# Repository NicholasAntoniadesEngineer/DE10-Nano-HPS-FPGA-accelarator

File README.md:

# DE10-Nano HPS-FPGA Accelerator

FPGA-accelerated IEEE 754 floating-point calculator on the Intel Cyclone V SoC (DE10-Nano). The FPGA fabric implements ADD, SUB, MUL, and DIV in pure RTL with a 7-cycle pipeline. The HPS (dual-core ARM Cortex-A9) runs Debian Linux and communicates with the calculator IP over the Lightweight HPS-to-FPGA Avalon-MM bridge.

## Prerequisites

- **Docker Desktop** (with Rosetta 2 on Apple Silicon)
- **Git** (with LFS: `git lfs install`)
- **50 GB+ free disk space** (Quartus 18.1 image + build artifacts)
- **DE10-Nano** + MicroSD card (8 GB+)

## Build

All builds run inside a Docker container (Quartus 18.1 + ARM GCC). No native toolchain needed.

```bash
cd docker

# First time: build the Docker image (~20 min)
./scripts/setup.sh

# Full system build: FPGA + kernel + rootfs + SD image (~60 min first time)
./scripts/docker-build.sh

# Or build individual components
./scripts/docker-build.sh fpga          # FPGA bitstream only (~23 min)
./scripts/docker-build.sh applications  # HPS applications only (~1 min)
```

**Output**: `HPS/linux_image/build/de10-nano-custom.img`

## Flash SD Card (macOS)

```bash
diskutil list                                            # identify SD card (e.g. /dev/disk4)
diskutil unmountDisk force /dev/diskN                     # unmount all partitions
sudo dd if=HPS/linux_image/build/de10-nano-custom.img of=/dev/rdiskN bs=4m
```

> Terminal must have **Full Disk Access** (System Settings > Privacy & Security > Full Disk Access).
> The disk number changes on replug -- always run `diskutil list` first.

## Prepare DE10-Nano

1. **Set MSEL DIP switch (SW10)** for HPS FPGA programming mode. Wrong MSEL = FPGA loads but registers return 0x0.
2. Insert SD card, connect USB cable (Ethernet + UART), power on.
3. Boot takes ~10 seconds. LEDs animate during `boot-led` startup.

> After changing DIP switches, **power cycle** the board (reboot is not enough -- MSEL is sampled at power-on).

## Connect via SSH

```bash
# Auto-detect USB Ethernet, configure interface, and SSH in
./scripts/ssh-to-board.sh

# Or manually (interface name varies -- check ifconfig)
sudo ifconfig en13 192.168.2.1 netmask 255.255.255.0
ssh root@192.168.2.2   # password: root
```

### Share Internet with Board

```bash
# Set up NAT so the board can reach the internet through your Mac
./scripts/share-internet.sh

# Tear down when done
./scripts/share-internet.sh --stop
```

## Run Applications

### Calculator Test Suite
```bash
calculator_test        # run all tests with 500 ms LED delays
calculator_test -q     # quick mode (no delays)
calculator_test -v     # verbose (register-level output)
```

### Calculator Demo (auto-starts at boot)
```bash
systemctl status calculator-demo     # check status
journalctl -u calculator-demo -f     # watch live output
```

### Boot LED (runs once at boot)
```bash
systemctl status boot-led            # check status
journalctl -u boot-led               # view log
```

### Register Access
```bash
devmem2 0xff20003c w    # read VERSION register (expect 0x00010001)
```

### Verify FPGA Bridges
```bash
cat /sys/class/fpga_bridge/*/state   # expect: "enabled"
```

## Project Structure

```
Makefile                  # Top-level orchestration
FPGA/
  quartus/                # Quartus project files + QSys system
  hdl/                    # Top-level Verilog (DE10_NANO_SoC_GHRD.v)
  ip/custom/calculator/   # Calculator IP (8 Verilog files + _hw.tcl)
  ip/custom/template/     # Template IP scaffold for new accelerators
  mk/                     # Modular Makefile fragments (qsys, quartus, etc.)
  generated/              # QSys-generated HDL (overlaid by qsys_check.sh)
  build/output_files/     # Quartus output (.rbf for SD card)
HPS/
  drivers/calculator/     # UIO-based calculator driver (/dev/uioN + mmap)
  drivers/fpga_uio/       # Shared UIO library (generic mmap abstraction)
  drivers/template/       # UIO driver template for new IP
  libs/logger/            # Shared logging library
  applications/
    calculator_test/      # Test suite (33 test cases)
    calculator_demo/      # Demo service (systemd, auto-start)
    boot_led/             # LED heartbeat at boot (systemd)
  tools/devmem2/          # /dev/mem read/write tool (cross-compiled)
  linux_image/
    kernel/               # Linux kernel (socfpga_defconfig)
    kernel/dts/           # Device tree sources (single source of truth)
    rootfs/               # Debian rootfs (debootstrap + overlays)
    bootloader/           # U-Boot + SPL + device tree
    scripts/              # SD image creation, rootfs build
scripts/
  generate-ip-framework.sh  # Scaffold new FPGA IP + QSys + UIO driver
  generate-app-framework.sh # Scaffold new HPS application + systemd service
  new_ip.sh                 # Symlink to generate-ip-framework.sh
  ssh-to-board.sh           # Auto-detect USB Ethernet, configure, SSH in
  share-internet.sh         # NAT setup: share Mac internet with board
  env-check.sh              # Validate host build environment
docker/
  scripts/                # setup.sh, docker-build.sh, docker-clean.sh
  Dockerfile              # Quartus 18.1 + ARM GCC container
documentation/
  deployment_guide.md     # Detailed deployment walkthrough
  hps_fpga_communication.md
```

## Troubleshooting

| Symptom | Cause | Fix |
|---------|-------|-----|
| `devmem2 0xff20003c w` returns `0x00000000` | MSEL DIP switch wrong | Set SW10 correctly, **power cycle** |
| All bridges show "disabled" | U-Boot didn't enable bridges | Check boot.scr, verify FPGA loaded |
| `calculator_test` all fail same result | Calculator not responding | Check bridge state, re-flash FPGA |
| SSH connection refused | USB Ethernet not configured | Run `ifconfig en13 192.168.2.1 ...` |
| `dd: permission denied` | Missing Full Disk Access | Add Terminal to Full Disk Access |
| Board can't reach internet | NAT not configured | Run `./scripts/share-internet.sh` |

## References

- [Deployment Guide](documentation/deployment_guide.md) -- step-by-step build and flash
- [Docker Build Environment](docker/README.md) -- container setup and scripts
- [FPGA-HPS Communication](documentation/hps_fpga_communication.md) -- register map and bridge details
- [DE10-Nano User Manual](documentation/references/DE10-Nano_User_manual_a_b.pdf)
- [Terasic DE10-Nano](https://www.terasic.com.tw/cgi-bin/page/archive.pl?Language=English&CategoryNo=165&No=1046#contents)
- [Cyclone V HPS Register Map](https://www.intel.com/content/www/us/en/programmable/hps/cyclone-v/hps.html#sfo1418687413697.html)

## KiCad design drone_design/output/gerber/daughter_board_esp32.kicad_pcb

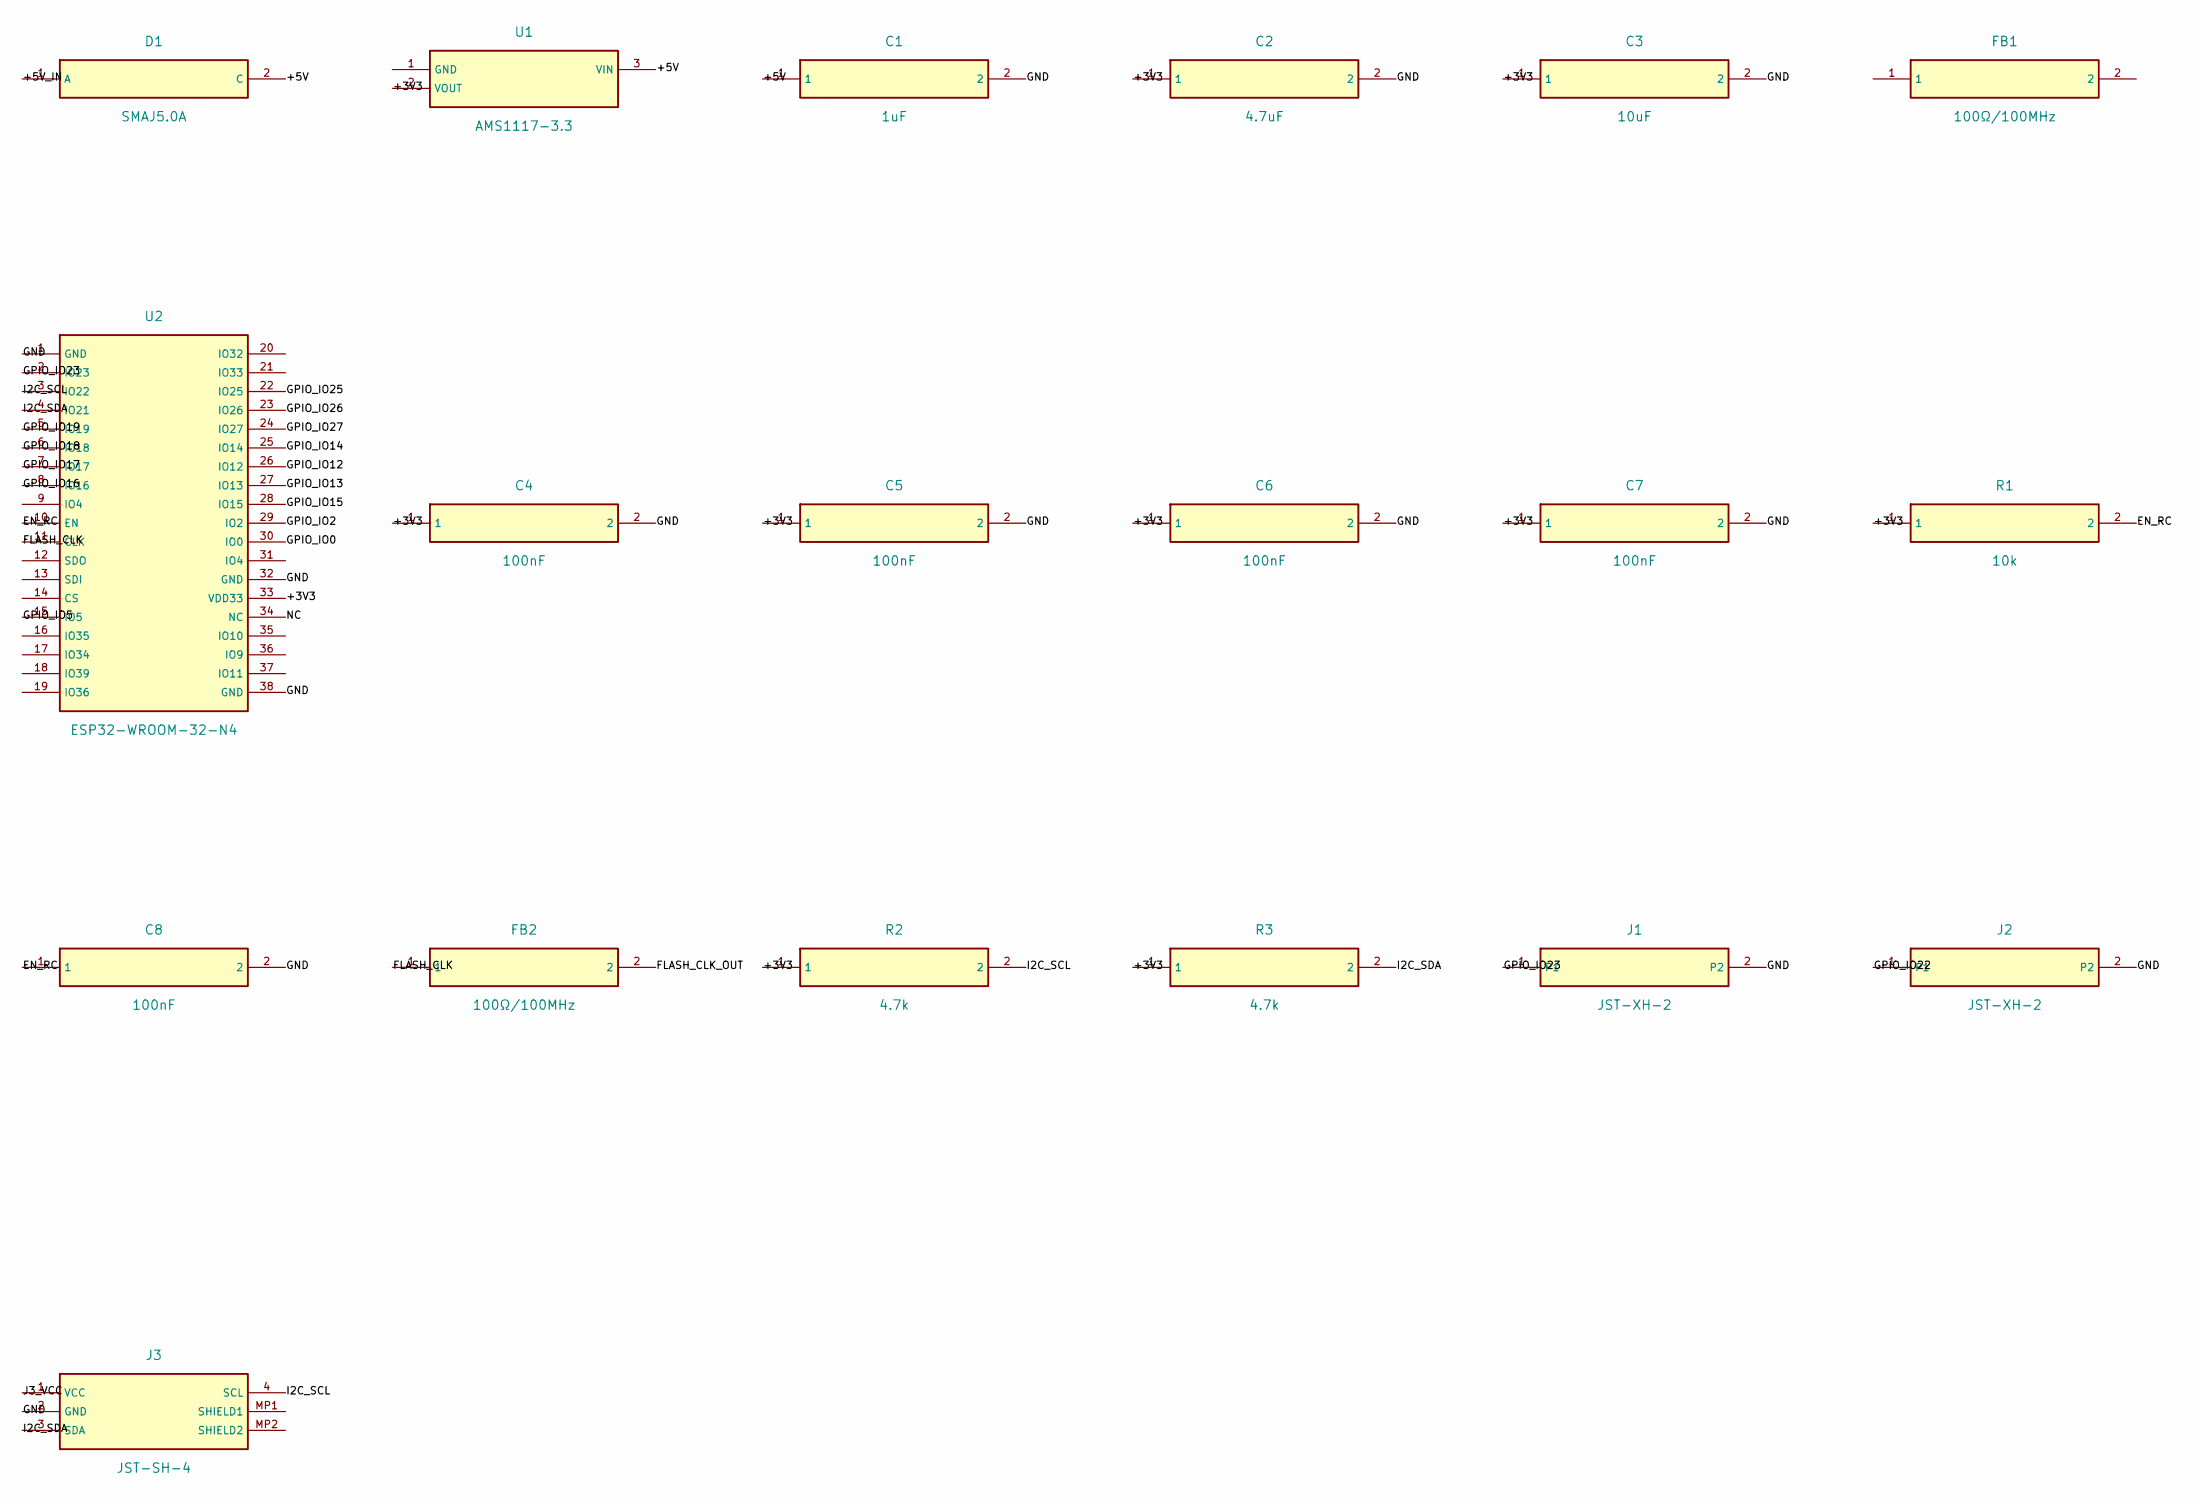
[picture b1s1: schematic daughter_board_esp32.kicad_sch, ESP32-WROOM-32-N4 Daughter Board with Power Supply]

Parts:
C1: 1uF
C2: 4.7uF
C3: 10uF
C4, C5, C6, C7, C8: 100nF
D1: SMAJ5.0A
FB1, FB2: 100Ω/100MHz
J1, J2: JST-XH-2
J3: JST-SH-4
R1: 10k
R2, R3: 4.7k
U1: AMS1117-3.3
U2: ESP32-WROOM-32-N4

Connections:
+3V3: C2.1, C3.1, C4.1, C5.1, C6.1, C7.1, R1.1, R2.1, R3.1, U1.2 (VOUT), U2.33 (VDD33)
+5V: C1.1, D1.2 (C), U1.3 (VIN)
+5V_IN: D1.1 (A)
EN_RC: C8.1, R1.2, U2.10 (EN)
FLASH_CLK: FB2.1, U2.11 (CLK)
FLASH_CLK_OUT: FB2.2
GND: C1.2, C2.2, C3.2, C4.2, C5.2, C6.2, C7.2, C8.2, J1.2, J2.2, J3.2 (GND), U2.1 (GND), U2.32 (GND), U2.38 (GND)
GPIO_IO0: U2.30 (IO0)
GPIO_IO2: U2.29 (IO2)
GPIO_IO5: U2.15 (IO5)
GPIO_IO12: U2.26 (IO12)
GPIO_IO13: U2.27 (IO13)
GPIO_IO14: U2.25 (IO14)
GPIO_IO15: U2.28 (IO15)
GPIO_IO16: U2.8 (IO16)
GPIO_IO17: U2.7 (IO17)
GPIO_IO18: U2.6 (IO18)
GPIO_IO19: U2.5 (IO19)
GPIO_IO22: J2.1
GPIO_IO23: J1.1, U2.2 (IO23)
GPIO_IO25: U2.22 (IO25)
GPIO_IO26: U2.23 (IO26)
GPIO_IO27: U2.24 (IO27)
I2C_SCL: J3.4 (SCL), R2.2, U2.3 (IO22)
I2C_SDA: J3.3 (SDA), R3.2, U2.4 (IO21)
J3_VCC: J3.1 (VCC)
NC: U2.34 (NC)

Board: 4 copper layers, 23 parts (0 on the bottom side), 8 nets, no tracks yet.

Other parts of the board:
MH: M2.5; MountingHole_2.7mm
MH#2, MH#3, MH#4: M2.5; MountingHole_2.7mm

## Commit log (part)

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2025-02-11 organising files
2025-02-11 Extending references
2025-02-11 Add DE10 Nano system builder and notes
2025-02-12 Cleanout success
2025-02-12 Adding references
2025-02-13 Re arrange folders and add a combined example
2025-02-14 Add hps fpga led example
2025-02-15 add update example using user space
2025-02-20 remove build files
2025-02-20 add example.md
2025-03-01 compiling some examples
2026-01-16 It builds!
2026-01-17 Major project reorganization and build system improvements
    Squashed 13 commits from DE10_NANO_SoC_GHRD branch into main.
    Key Changes:
    - Project structure reorganization: Moved FPGA files to fpga/ subdirectory
    - Build system: Enhanced Makefile with improved dependency tracking
    - QSys system: Updated soc_system configuration and generated files
    - Path fixes: Corrected file paths in .qsf after folder reorganization
2026-01-17 reorganising, to be built
2026-01-23 Complete DE10-Nano build system overhaul and documentation
    Build System Improvements:
    - Fixed RBF file detection in SD image build with corrected relative paths
    - Added intelligent FPGA artifact verification with freshness warnings
    - Enhanced error handling and build reliability across WSL/Windows
    - Added SOCEDS_DEST_ROOT environment configuration for future SoC EDS usage
    - Improved internet connectivity checks with retry logic
2026-01-23 Clean up project files and update documentation references
    - Delete redundant docs (QUICK_START.md, README_BUILD.md, BUILD_INSTRUCTIONS.md)
    - Delete temporary normalized scripts from linux_image/scripts/
    - Remove Qt user file from tracking (USB_Gadget.pro.user)
    - Update .gitignore to exclude temp normalized scripts and .pro.user files
    - Remove emojis from documentation to maintain consistency
    - Fix outdated file references in README files
2026-01-23 remove settings file
2026-01-23 build root update
2026-01-23 README.md update
2026-01-24 docs: Update deployment guide for incremental kernel builds
    - Add incremental build features to build capabilities section
    - Update troubleshooting with check-rebuild commands
    - Document new rebuild/force-rebuild targets
    - Explain massive time savings from incremental builds
    - Update recovery commands to prioritize check-rebuild
2026-01-25 Remove old .tar.gz files from git tracking
    - Remove rootfs.tar.gz and rootfs_base.tar.gz from git
    - These are old files replaced by .tar.xz compression
    - Files remain on disk but are no longer tracked by git
2026-01-25 Update ignore/LFS rules and refresh generated FPGA metadata
2026-01-26 Update docker file and readme
2026-01-27 Docker reorganisation and improvements
2026-01-27 Add compressed SD image, flash script, clean up deprecated scripts
    - Add compressed SD card image (.img.xz, 178MB) tracked via Git LFS
    - Add flash_sd.sh helper script for flashing to SD cards (macOS/Linux)
    - Add sd-image-compress target to Makefile for creating .img.xz
    - Remove deprecated scripts: build_linux_image.sh, create_sd_image_wrapper.sh
    - Update .gitignore to track compressed image while ignoring 4GB uncompressed
2026-01-29 Deployable docker container successful
2026-03-11 v1.1.0 — UIO driver, owned DTS, modular build system
    Squashed from dev branch. Key changes since v1.0:
    HPS Driver:
    - Rewrite calculator driver to use Linux UIO framework (/dev/uioN)
    instead of /dev/mem; no hardcoded physical addresses
    - Interrupt-driven completion via select()+read() on UIO fd
    - Driver discovers device by linux,uio-name in /sys/class/uio/*/name
2026-03-11 fix: add fpga_uio include path and source to application Makefiles
2026-03-14 add internet sharing script, research references, and README updates
    - scripts/share-internet.sh: automate Mac-to-DE10-Nano NAT setup
    - scripts/new_ip.sh: restore symlink to generate-ip-framework.sh
    - documentation/research_references.md: 150+ curated references across ML inference, mechatronics, GPS-free geolocation, and underwater navigation
    - README.md: add SSH/internet sharing sections, update project structure
    - Rebuild artifacts (SD image, rootfs)
2026-03-14 feat: self-contained 3D viewer with embedded STL parts
    - Rewrite export_stl.py to generate positioned assembly parts and embed
    all 41 components as base64 in viewer.html (3.8 MB, fully static)
    - Per-component click selection with bounding box, triangle count, normals
    - Parts list sidebar with visibility toggles
    - Fix Three.js readonly position property error (Object.assign → explicit set)
    - Works from file:// protocol — no HTTP server required
2026-03-14 fix: replace triangle wireframe with edge-only outline view
    Triangle mesh wireframe was impractical — showed thousands of
    tessellation edges. Now uses EdgesGeometry (15° threshold) to show
    only hard edges with semi-transparent solid fill, giving a clean
    engineering wireframe view.
2026-03-14 feat: modular two-section arms and nose boom with adjustable length
    Arms split into inner (tab) + outer (motor) sections with 40mm
    I-beam overlap zone. 4x M2 slider holes at 10mm pitch allow
    adjustable motor distance. Same pattern for nose boom: root (190mm)
    + tip (230mm) sections with web/collar interlock.
    - arm.py: make_arm_inner(), make_arm_outer(), make_arm() (compat)
    - nose_boom.py: make_boom_root(), make_boom_tip(), make_nose_boom()
2026-03-15 fix: correct rotation convention mismatch between constraint solver and CadQuery
    The euler rotation matrix functions used clockwise (passive) convention
    while CadQuery's shape.rotate() uses counter-clockwise (active/right-hand
    rule). This caused constrained parts to rotate in the wrong direction —
    anchors appeared correct but part geometry was misaligned.
    Also restructures codebase: extracts cadquery_framework as a reusable
    module with assembly/, exporters/, viewer/, kicad/ subpackages. Moves
2026-03-15 fix: correct XZ workplane extrude direction for barb, wires, barrel jack
    CadQuery Workplane("XZ") has normal pointing -Y, so .extrude() goes
    in -Y direction. The reservoir barb, pump wire stubs, and DE10 barrel
    jack were all extruding INTO their parent bodies instead of outward.
    Fixed by adjusting translate offsets to account for -Y extrusion.
    This fixes anchors not matching their visual geometry locations.
2026-03-15 feat: viewer restructure, arm extension, orientation fix, tubing routing
    - Move viewer files to static/ subdir, add codegen/ and overlay modules
    - Correct drone orientation: front=+X (boom/camera), update ToF labels
    - Add 40mm arm adjustment extension for physical motor distance tuning
    - Fix tubing routing to clear ESC bounding boxes (X=65 rise point)
    - Add modifiers module to cadquery_framework
2026-03-15 fix: correct underslung part orientations and reduce mount gap
    - Fix pump_bracket, reservoir, and pump mounting: all three were
    inverted (walls/fill-port facing plate instead of hanging down).
    Use base_mount/bottom_face anchors (normal (0,0,-1)) which trigger
    the 180° flip needed to hang correctly below the bottom plate.
    - Reduce underslung_gap from 5mm to 3mm to close the excessive gap
    between underslung parts and the bottom plate.
2026-03-15 fix: simplify res→pump tubing route, remove low_z detour
2026-03-15 fix: make res→pump tube route fully orthogonal, use anchors correctly at each end
2026-03-15 fix: swap pump inlet/outlet tube anchor assignments, fix pump→nozzle orthogonal routing
2026-03-15 fix: remove tube_rp_j3 overshoot and simplify pump→nozzle to 5 waypoints
2026-03-15 feat: wire routes_data through export pipeline to viewer HTML
    - drone_3d_model.py: load tube_routes.json and pass routes_data to export_assembly()
    - pipeline.py: accept routes_data param and forward to generate_viewer_html()
    - viewer now embeds window.__VIEWER_ROUTES for Route Editor mode
2026-03-16 feat: centralise JLCPCB manufacturing constraints for all PCB generators
    Add cadquery_framework/kicad/jlcpcb_constraints.py as single source of
    truth for all PCB tolerances (stackup, trace widths, clearances, drill
    sizes, silkscreen, solder mask). Both primitives.py (2-layer structural)
    and daughter_board.py (4-layer electronics) now import from it.
    gerber_export.py auto-writes jlcpcb_constraints.kicad_dru alongside every
    .kicad_pcb so KiCad DRC stays in sync with Python constants.
2026-03-17 feat: algorithmic PCB placement optimizer with zero-error validation
    Replace hand-coded component placements with a 4-stage algorithmic
    optimizer: force-directed zone assignment, deterministic row-packing,
    and simulated annealing refinement. Produces 131 placements with 0
    courtyard overlaps, 0 cutout violations, and 3157mm HPWL.
    - Add cadquery_framework/kicad/placement/ package (9 modules):
    geometry, zone_assigner, row_packer, annealing, config, pipeline,
2026-03-17 feat: comprehensive daughter board electronics with 100% JLCPCB LCSC stock coverage
    Squashed from dev branch: 21 commits covering:
    - Complete KiCad component library (58 components, all with LCSC codes)
    - BOM and CPL generation for JLCPCB assembly
    - JLCPCB manufacturing constraints and design validation
    - Algorithmic PCB placement optimizer (force-directed → simulated annealing)
    - Production daughter board schematic and PCB layout
2026-03-17 feat: switch WiFi module from WILC3000 to ESP32-WROOM-32-N4 with complete supporting circuits
    Replace ATWILC3000 (not LCSC-stocked) with ESP32-WROOM-32-N4 (C82899):
    - Massive LCSC stock (16,426 units) vs WILC3000 unavailable
    - Professional-grade dual-core MCU (Xtensa 32-bit LX6)
    - Native WiFi 802.11 b/g/n + dual-mode Bluetooth/BLE
    - Can use HPS SPI1 or FPGA SPI interface (flexible)
    - Lower cost (.83 vs .94 for WILC3000-MR110CA variant)
2026-03-17 feat: automatic silk label repositioner — 0 DRC errors
    Add silk_repositioner.py that finds collision-free positions for all
    131 component reference labels using greedy spiral search (8 directions
    × 10 distances). Replaces manual repositioning in KiCad.
    - Checks against pads, mounting holes, board edges, and already-placed labels
    - Integrated into PCB build pipeline (runs before silkscreen validator)
    - Updated silkscreen_checker to accept repositioned label offsets
2026-03-17 fix: propeller cutouts now physically cut board corners + silk labels avoid cutout zones
    Two critical fixes:
    1. Board outline: Replace the broken approach (full rectangle + overlaid arcs)
    with a single closed boundary where each corner is replaced by a propeller
    clearance arc. Edges are trimmed to intersection points (±28.82mm from
    centre). Result: 4 lines + 4 arcs forming a proper closed loop.
    2. Silk repositioner: Add propeller cutout zone awareness so labels are never
2026-03-17 feat: automatically generate STEP models for all component packages + fix model path resolution
    - Call generate_all_package_models() in gerber export pipeline to create parametric 3D STEP files for 29 component packages
    - Fixed path resolution for fp_3d_model references from ${KIPRJMOD}/../../cadquery_framework/kicad/models_3d/step/ to ${KIPRJMOD}/models_3d/step/
    - STEP files now generated in gerber/models_3d/step/ directory alongside PCB files
    - All components with model_3d field populated now correctly reference their 3D models in KiCad 3D viewer
    - Silk label validation still reports 0 errors with auto-repositioned labels passing all DRC checks
